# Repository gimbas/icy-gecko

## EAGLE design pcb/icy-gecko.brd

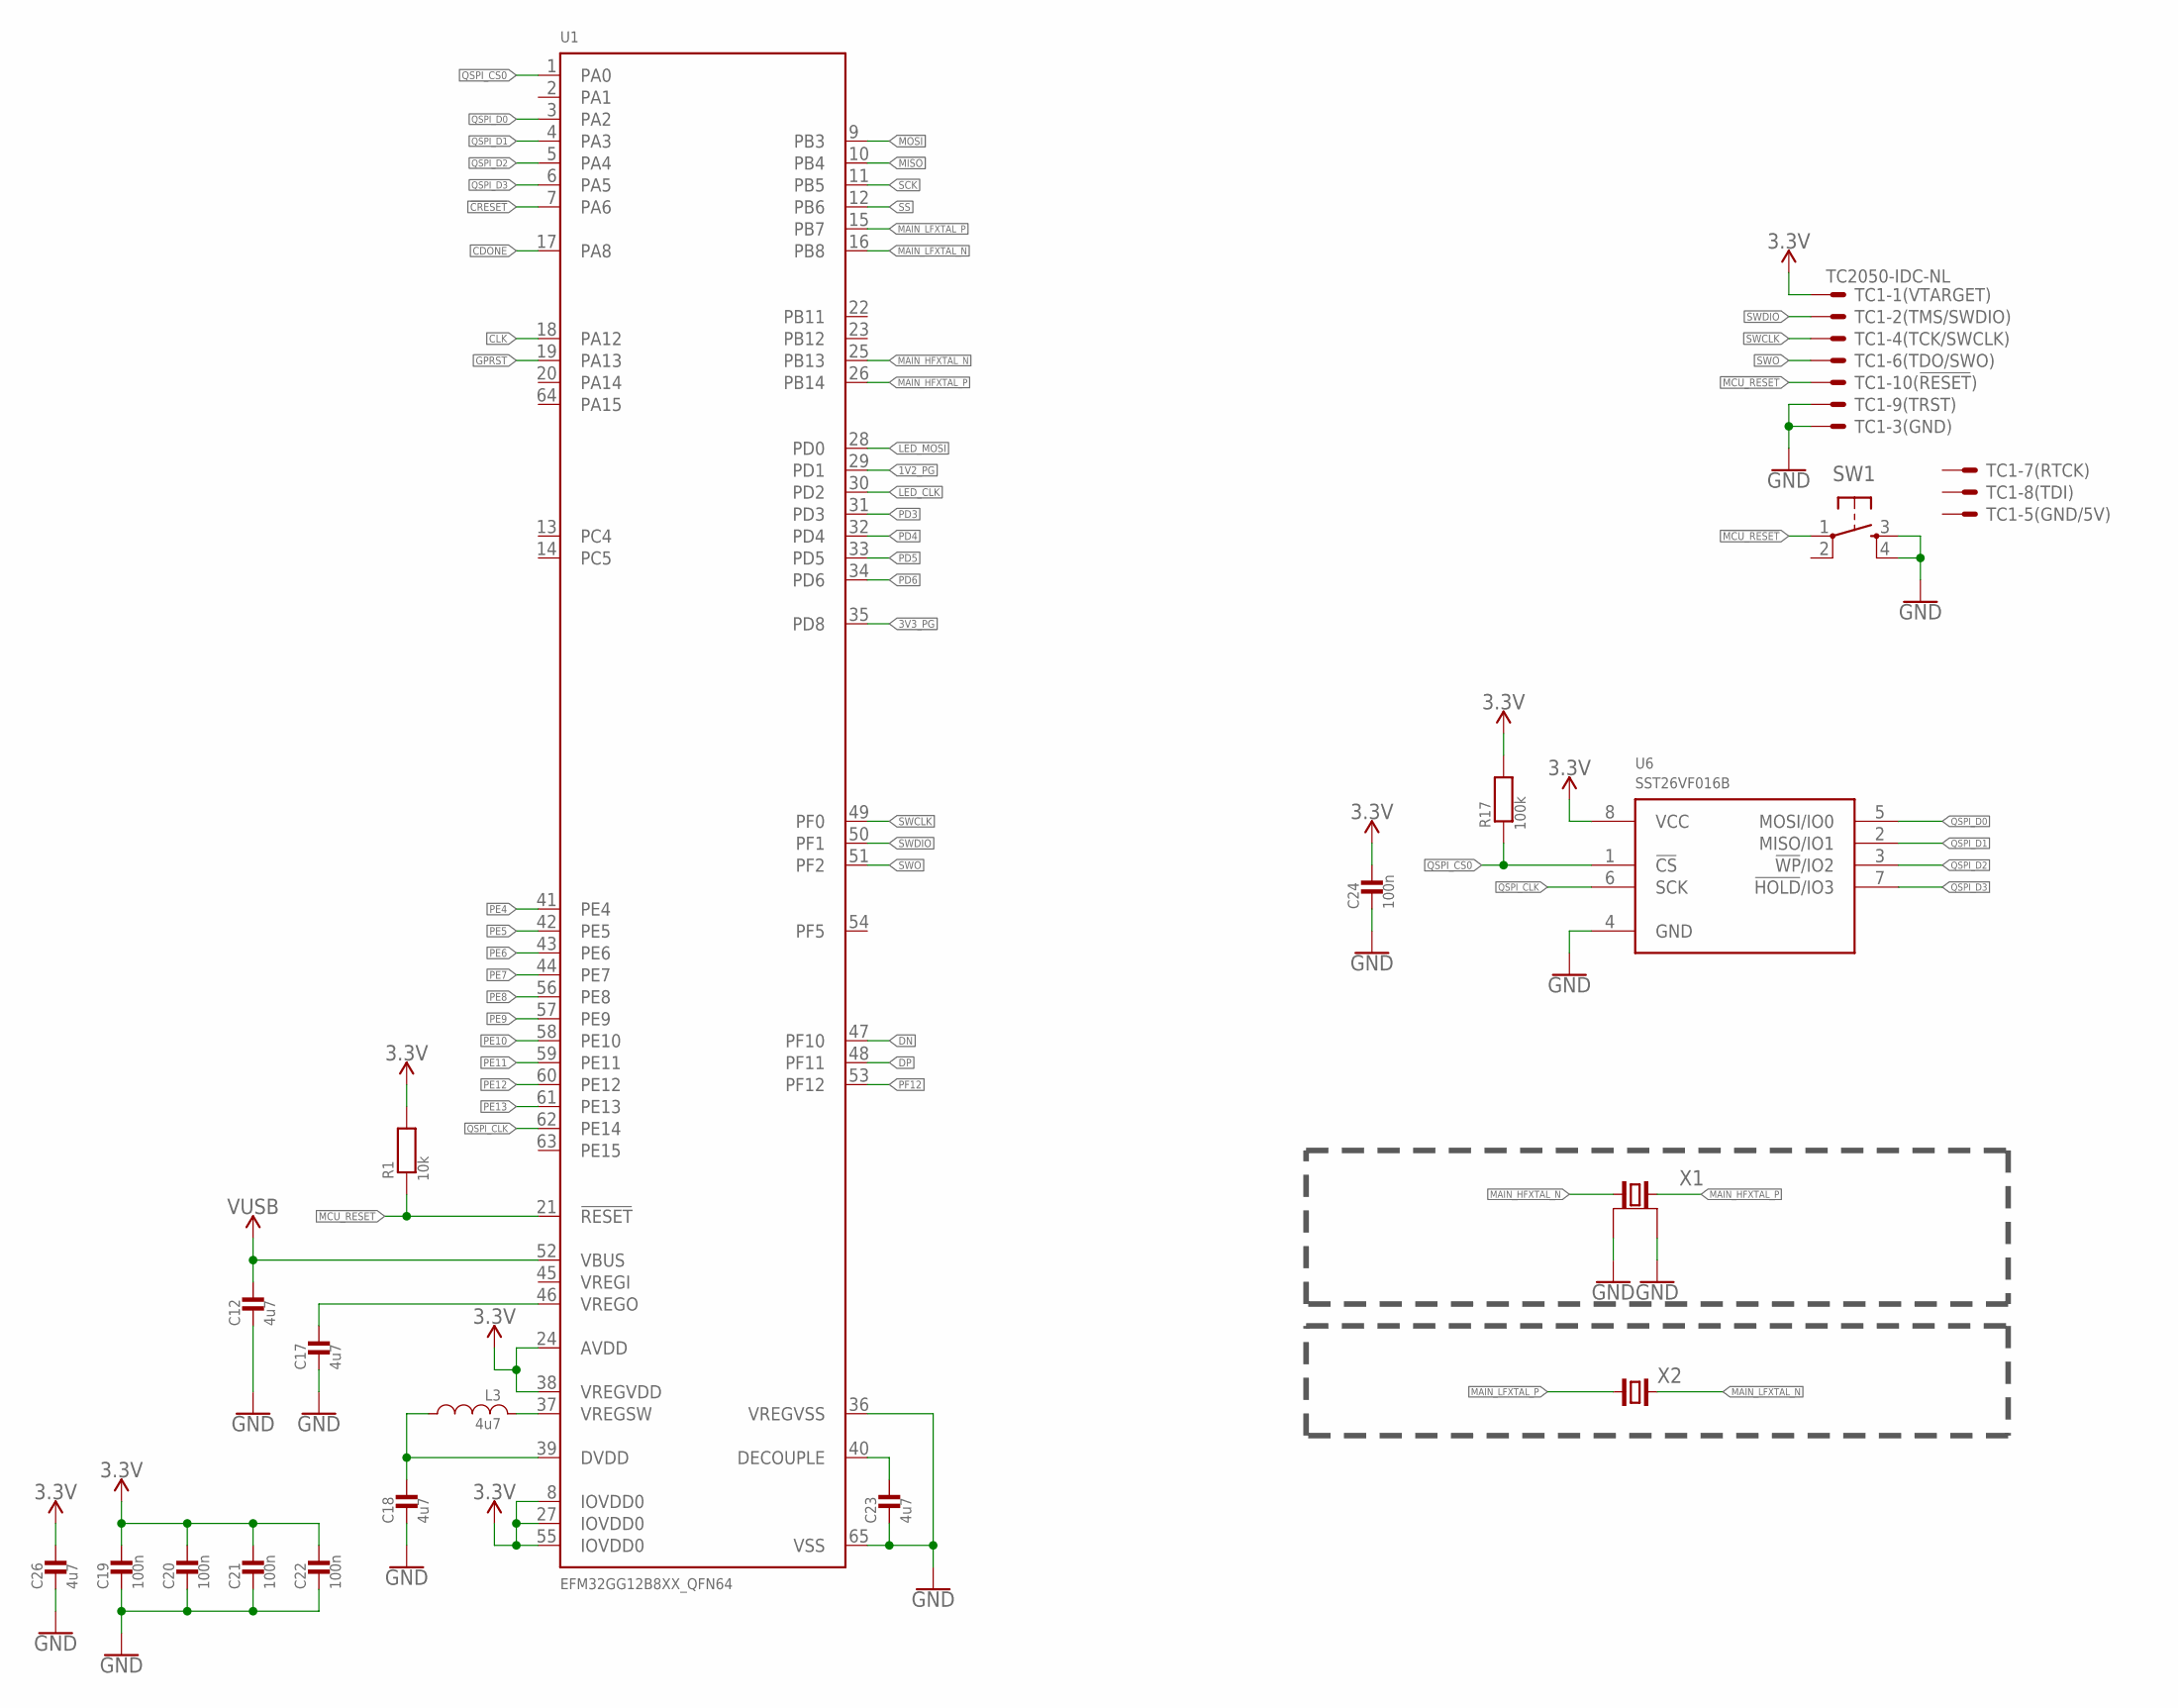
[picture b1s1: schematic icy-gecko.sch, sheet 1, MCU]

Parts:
C12, C17, C18, C23, C26: 4u7; 0603_WAVE
C19, C20, C21, C22, C24: 100n; 0603_WAVE
L3: 4u7; _0806
R1: 10k; 0603_WAVE
R17: 100k; 0603_WAVE
SW1: PUSH_BUTTON
TC1: TC2050-IDC-NL
U1: EFM32GG12B8XX_QFN64; QFN64
U6: SST26VF016B; WSOIC8
X1: CRYSTAL_4P; 4-SMD-3225
X2: CRYSTAL2-SMD-3215; 2-SMD-3215

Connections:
1V2_PG: U1.29 (PD1); also elsewhere on the board
3.3V: C19.P$1, C20.P$1, C21.P$1, C22.P$1, C24.P$1, C26.P$1, R1.P$2, R17.P$2, TC1.1, U1.8 (IOVDD0), U1.24 (AVDD), U1.27 (IOVDD0), U1.38 (VREGVDD), U1.55 (IOVDD0), U6.8 (VCC); also elsewhere on the board
3V3_PG: U1.35 (PD8); also elsewhere on the board
!CRESET: U1.7 (PA6); also elsewhere on the board
!MCU_RESET: R1.P$1, SW1.1, TC1.10, U1.21 (!RESET)
CDONE: U1.17 (PA8); also elsewhere on the board
CLK: U1.18 (PA12); also elsewhere on the board
DN: U1.47 (PF10); also elsewhere on the board
DP: U1.48 (PF11); also elsewhere on the board
GND: C12.P$2, C17.P$2, C18.P$2, C19.P$2, C20.P$2, C21.P$2, C22.P$2, C23.P$2, C24.P$2, C26.P$2, SW1.3, SW1.4, TC1.3, TC1.9, U1.36 (VREGVSS), U1.65 (VSS), U6.4 (GND), X1.2 (GND), X1.4 (GND); also elsewhere on the board
GPRST: U1.19 (PA13); also elsewhere on the board
LED_CLK: U1.30 (PD2); also elsewhere on the board
LED_MOSI: U1.28 (PD0); also elsewhere on the board
MAIN_HFXTAL_N: U1.25 (PB13), X1.1
MAIN_HFXTAL_P: U1.26 (PB14), X1.3 (2)
MAIN_LFXTAL_N: U1.16 (PB8), X2.2
MAIN_LFXTAL_P: U1.15 (PB7), X2.1
MISO: U1.10 (PB4); also elsewhere on the board
MOSI: U1.9 (PB3); also elsewhere on the board
unnamed: C17.P$1, U1.46 (VREGO)
unnamed: L3.1, U1.37 (VREGSW)
unnamed: C23.P$1, U1.40 (DECOUPLE)
unnamed: C18.P$1, L3.2, U1.39 (DVDD)
PD3: U1.31 (PD3); also elsewhere on the board
PD4: U1.32 (PD4); also elsewhere on the board
PD5: U1.33 (PD5); also elsewhere on the board
PD6: U1.34 (PD6); also elsewhere on the board
PE4: U1.41 (PE4); also elsewhere on the board
PE5: U1.42 (PE5); also elsewhere on the board
PE6: U1.43 (PE6); also elsewhere on the board
PE7: U1.44 (PE7); also elsewhere on the board
PE8: U1.56 (PE8); also elsewhere on the board
PE9: U1.57 (PE9); also elsewhere on the board
PE10: U1.58 (PE10); also elsewhere on the board
PE11: U1.59 (PE11); also elsewhere on the board
PE12: U1.60 (PE12); also elsewhere on the board
PE13: U1.61 (PE13); also elsewhere on the board
PF12: U1.53 (PF12); also elsewhere on the board
QSPI_CLK: U1.62 (PE14), U6.6 (SCK)
QSPI_CS0: R17.P$1, U1.1 (PA0), U6.1 (!CS!)
QSPI_D0: U1.3 (PA2), U6.5 (MOSI/IO0)
QSPI_D1: U1.4 (PA3), U6.2 (MISO/IO1)
QSPI_D2: U1.5 (PA4), U6.3 (!WP!/IO2)
QSPI_D3: U1.6 (PA5), U6.7 (!HOLD!/IO3)
SCK: U1.11 (PB5); also elsewhere on the board
SS: U1.12 (PB6); also elsewhere on the board
SWCLK: TC1.4, U1.49 (PF0)
SWDIO: TC1.2, U1.50 (PF1)
SWO: TC1.6, U1.51 (PF2)
VUSB: C12.P$1, U1.52 (VBUS); also elsewhere on the board

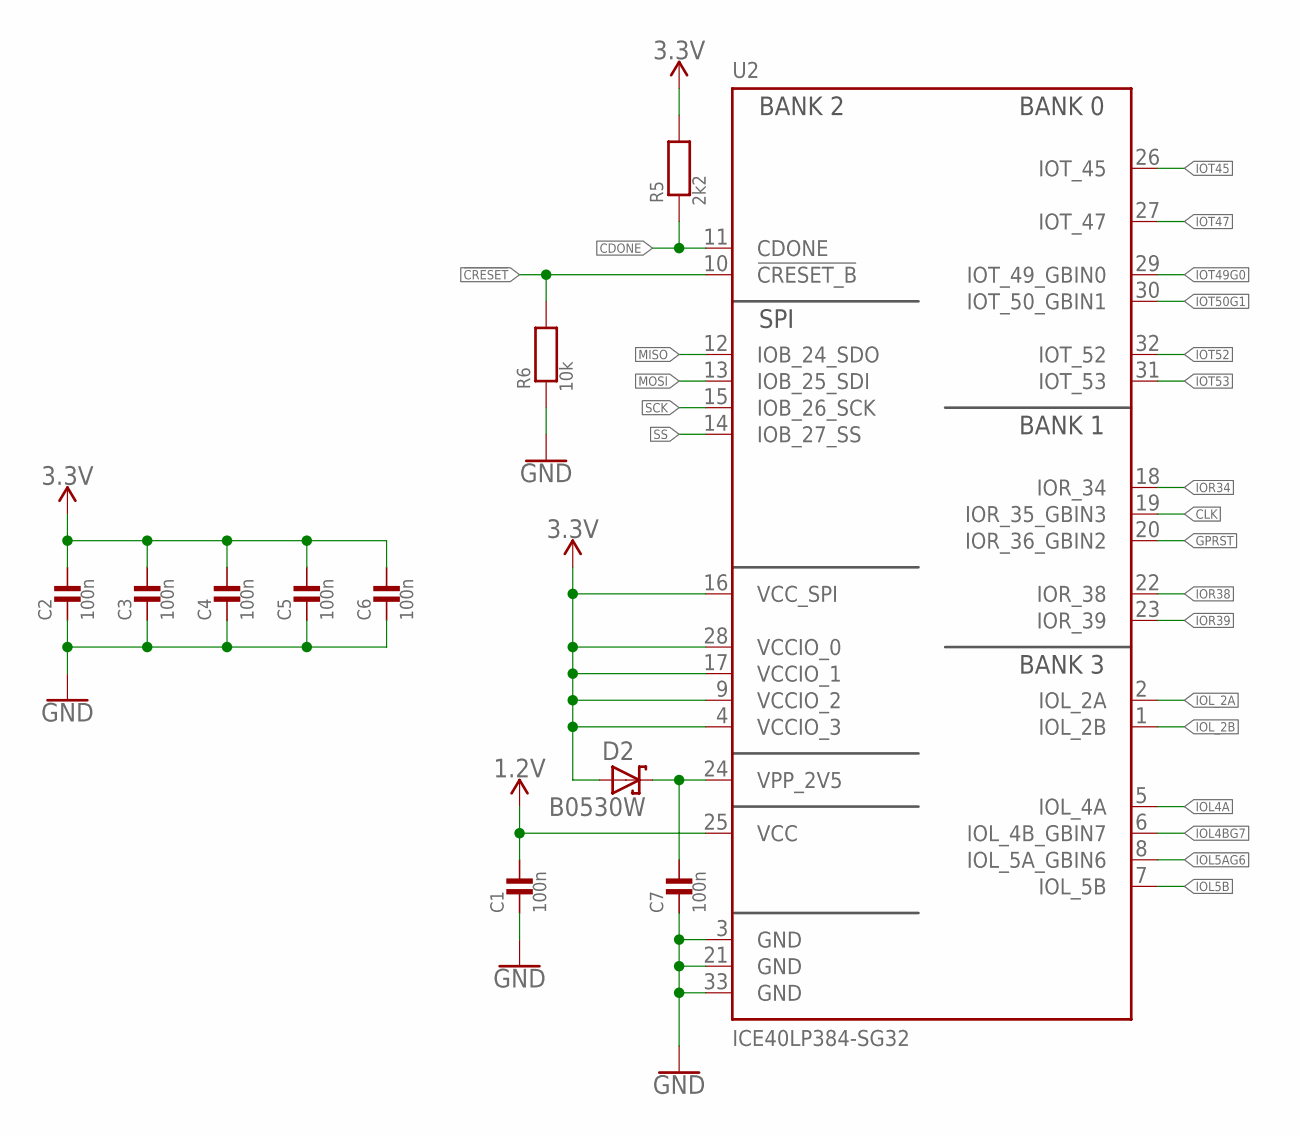
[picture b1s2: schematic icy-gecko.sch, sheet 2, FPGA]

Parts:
C1, C2, C3, C4, C5, C6, C7: 100n; 0603_WAVE
D2: B0530W; SOD-123
R5: 2k2; 0603_WAVE
R6: 10k; 0603_WAVE
U2: ICE40LP384-SG32; QFN32

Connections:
1.2V: C1.P$1, U2.25 (VCC); also elsewhere on the board
3.3V: C2.P$1, C3.P$1, C4.P$1, C5.P$1, C6.P$1, D2.A, R5.P$2, U2.4 (VCCIO_3), U2.9 (VCCIO_2), U2.16 (VCC_SPI), U2.17 (VCCIO_1), U2.28 (VCCIO_0); also elsewhere on the board
!CRESET: R6.P$2, U2.10 (!CRESET_B); also elsewhere on the board
CDONE: R5.P$1, U2.11 (CDONE); also elsewhere on the board
CLK: U2.19 (IOR_35_GBIN3); also elsewhere on the board
GND: C1.P$2, C2.P$2, C3.P$2, C4.P$2, C5.P$2, C6.P$2, C7.P$2, R6.P$1, U2.3 (GND), U2.21 (GND), U2.33 (GND); also elsewhere on the board
GPRST: U2.20 (IOR_36_GBIN2); also elsewhere on the board
IOL4A: U2.5 (IOL_4A); also elsewhere on the board
IOL4BG7: U2.6 (IOL_4B_GBIN7); also elsewhere on the board
IOL5AG6: U2.8 (IOL_5A_GBIN6); also elsewhere on the board
IOL5B: U2.7 (IOL_5B); also elsewhere on the board
IOL_2A: U2.2 (IOL_2A); also elsewhere on the board
IOL_2B: U2.1 (IOL_2B); also elsewhere on the board
IOR34: U2.18 (IOR_34); also elsewhere on the board
IOR38: U2.22 (IOR_38); also elsewhere on the board
IOR39: U2.23 (IOR_39); also elsewhere on the board
IOT45: U2.26 (IOT_45); also elsewhere on the board
IOT47: U2.27 (IOT_47); also elsewhere on the board
IOT49G0: U2.29 (IOT_49_GBIN0); also elsewhere on the board
IOT50G1: U2.30 (IOT_50_GBIN1); also elsewhere on the board
IOT52: U2.32 (IOT_52); also elsewhere on the board
IOT53: U2.31 (IOT_53); also elsewhere on the board
MISO: U2.12 (IOB_24_SDO); also elsewhere on the board
MOSI: U2.13 (IOB_25_SDI); also elsewhere on the board
unnamed: C7.P$1, D2.C, U2.24 (VPP_2V5)
SCK: U2.15 (IOB_26_SCK); also elsewhere on the board
SS: U2.14 (IOB_27_SS); also elsewhere on the board

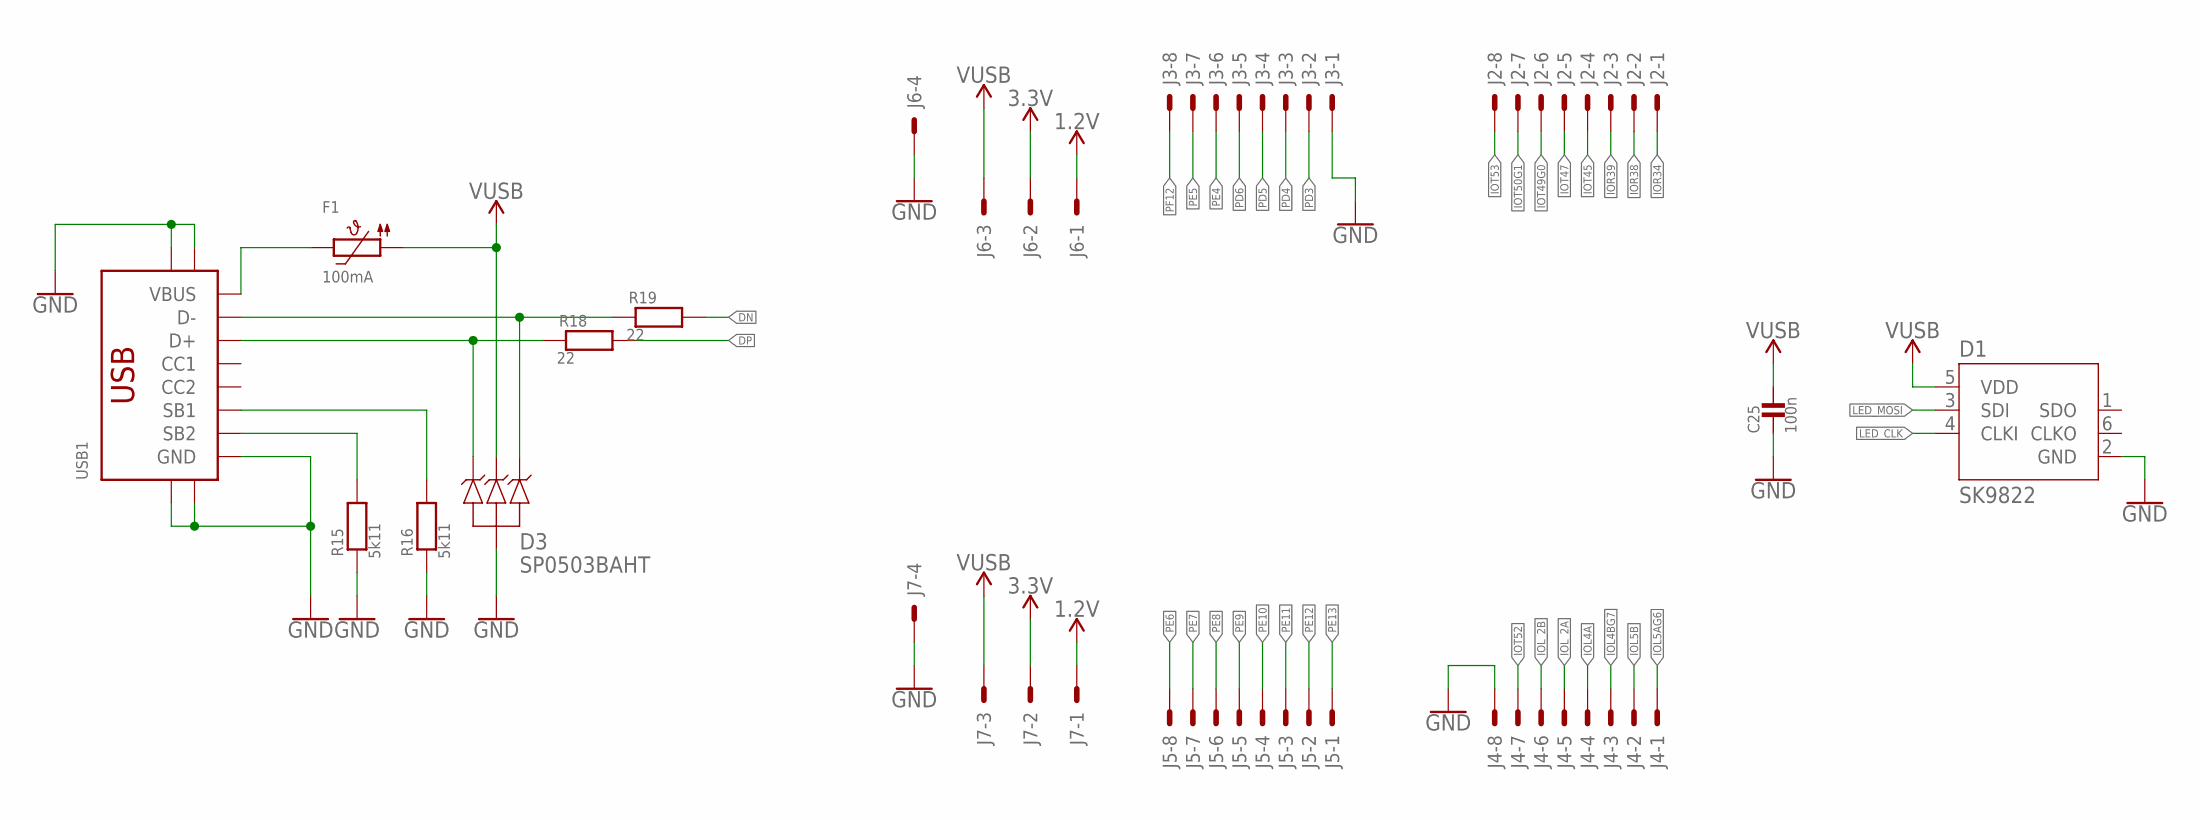
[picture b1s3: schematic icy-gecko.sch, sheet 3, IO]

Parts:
C25: 100n; 0603_WAVE
D1: SK9822; 2020
D3: SP0503BAHT; SOT143
F1: 100mA; 0805
J2, J3, J4, J5: 8; 1X8_2.54
J6, J7: 4; 1X4_2.54
R15, R16: 5k11; 0603_WAVE
R18, R19: 22; 0603_WAVE
USB1: USB-C-16P-SMD-FLAT-SIDE-TYPE-2

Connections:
1.2V: J6.1, J7.1; also elsewhere on the board
3.3V: J6.2, J7.2; also elsewhere on the board
DN: R19.P$2; also elsewhere on the board
DP: R18.P$2; also elsewhere on the board
GND: C25.P$2, D1.2 (GND), D3.1, J3.1, J4.8, J6.4, J7.4, R15.P$1, R16.P$1, USB1.A1/B12 (GND), USB1.B1/A12 (GND), USB1.SHIELD@0 (SHIELD), USB1.SHIELD@1 (SHIELD), USB1.SHIELD@2 (SHIELD), USB1.SHIELD@3 (SHIELD); also elsewhere on the board
IOL4A: J4.4; also elsewhere on the board
IOL4BG7: J4.3; also elsewhere on the board
IOL5AG6: J4.1; also elsewhere on the board
IOL5B: J4.2; also elsewhere on the board
IOL_2A: J4.5; also elsewhere on the board
IOL_2B: J4.6; also elsewhere on the board
IOR34: J2.1; also elsewhere on the board
IOR38: J2.2; also elsewhere on the board
IOR39: J2.3; also elsewhere on the board
IOT45: J2.4; also elsewhere on the board
IOT47: J2.5; also elsewhere on the board
IOT49G0: J2.6; also elsewhere on the board
IOT50G1: J2.7; also elsewhere on the board
IOT52: J4.7; also elsewhere on the board
IOT53: J2.8; also elsewhere on the board
LED_CLK: D1.4 (CLKI); also elsewhere on the board
LED_MOSI: D1.3 (SDI); also elsewhere on the board
unnamed: F1.2, USB1.A4/B9 (VBUS), USB1.B4/A9 (VBUS)
unnamed: R15.P$2, USB1.B8 (SB2)
unnamed: R16.P$2, USB1.A8 (SB1)
PD3: J3.2; also elsewhere on the board
PD4: J3.3; also elsewhere on the board
PD5: J3.4; also elsewhere on the board
PD6: J3.5; also elsewhere on the board
PE4: J3.6; also elsewhere on the board
PE5: J3.7; also elsewhere on the board
PE6: J5.8; also elsewhere on the board
PE7: J5.7; also elsewhere on the board
PE8: J5.6; also elsewhere on the board
PE9: J5.5; also elsewhere on the board
PE10: J5.4; also elsewhere on the board
PE11: J5.3; also elsewhere on the board
PE12: J5.2; also elsewhere on the board
PE13: J5.1; also elsewhere on the board
PF12: J3.8; also elsewhere on the board
USBDN: D3.4, R19.P$1, USB1.A7 (D-), USB1.B7 (D-)
USBDP: D3.2, R18.P$1, USB1.A6 (D+), USB1.B6 (D+)
VUSB: C25.P$1, D1.5 (VDD), D3.3, F1.1, J6.3, J7.3; also elsewhere on the board

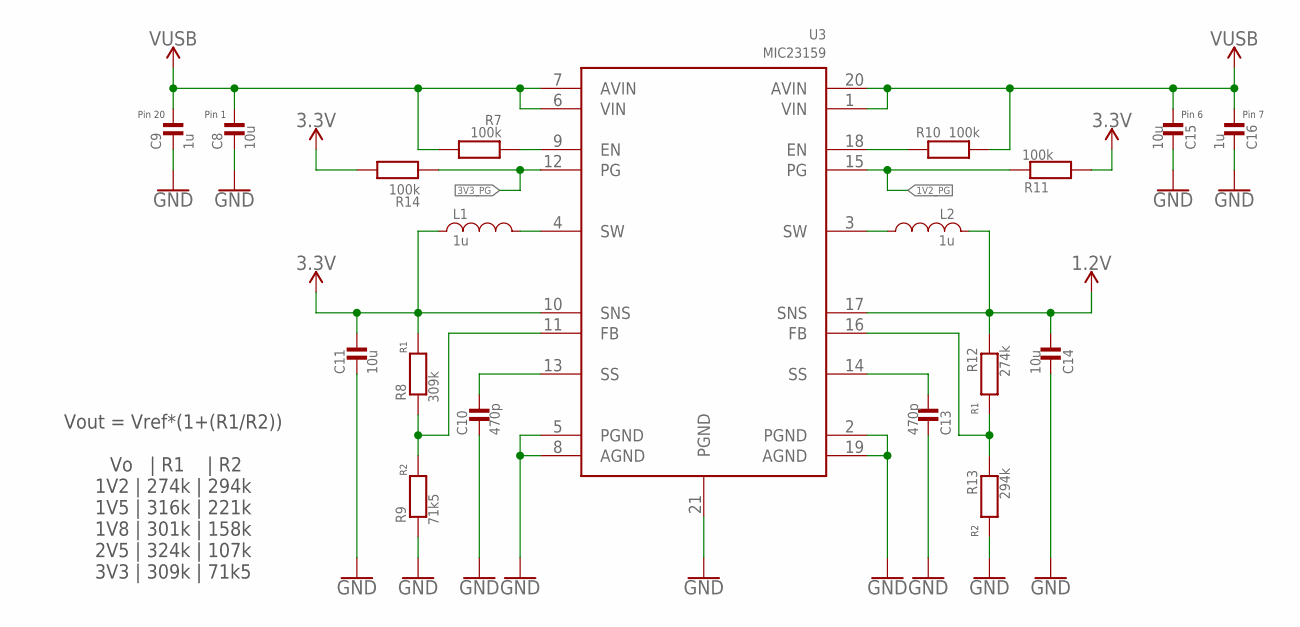
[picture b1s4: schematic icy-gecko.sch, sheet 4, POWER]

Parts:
C8, C11, C14, C15: 10u; 0603_WAVE
C9, C16: 1u; 0603_WAVE
C10, C13: 470p; 0603_WAVE
L1, L2: 1u; _0806
R7, R10, R11, R14: 100k; 0603_WAVE
R8: 309k; 0603_WAVE
R9: 71k5; 0603_WAVE
R12: 274k; 0603_WAVE
R13: 294k; 0603_WAVE
U3: MIC23159; VQFN20

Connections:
1.2V: C14.P$1, L2.1, R12.P$1, U3.17 (SNS); also elsewhere on the board
1V2_PG: R11.P$1, U3.15 (PG); also elsewhere on the board
3.3V: C11.P$1, L1.1, R8.P$2, R11.P$2, R14.P$2, U3.10 (SNS); also elsewhere on the board
3V3_PG: R14.P$1, U3.12 (PG); also elsewhere on the board
GND: C8.P$2, C9.P$2, C10.P$2, C11.P$2, C13.P$2, C14.P$2, C15.P$2, C16.P$2, R9.P$1, R13.P$2, U3.2 (PGND), U3.5 (PGND), U3.8 (AGND), U3.19 (AGND), U3.21 (PGND); also elsewhere on the board
MPU_PWR: R10.P$1, U3.18 (EN)
unnamed: R7.P$1, U3.9 (EN)
unnamed: L1.2, U3.4 (SW)
unnamed: C10.P$1, U3.13 (SS)
unnamed: R8.P$1, R9.P$2, U3.11 (FB)
unnamed: L2.2, U3.3 (SW)
unnamed: C13.P$1, U3.14 (SS)
unnamed: R12.P$2, R13.P$1, U3.16 (FB)
VUSB: C8.P$1, C9.P$1, C15.P$1, C16.P$1, R7.P$2, R10.P$2, U3.1 (VIN), U3.6 (VIN), U3.7 (AVIN), U3.20 (AVIN); also elsewhere on the board

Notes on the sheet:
Pin 20
Pin 1
Pin 7
Pin 6
Vout = Vref*(1+(R1/R2)) Vo | R1 | R2 1V2 | 274k | 294k 1V5 | 316k | 221k 1V8 | 301k | 158k 2V5 | 324k | 107k 3V3 | 309k | 71k5

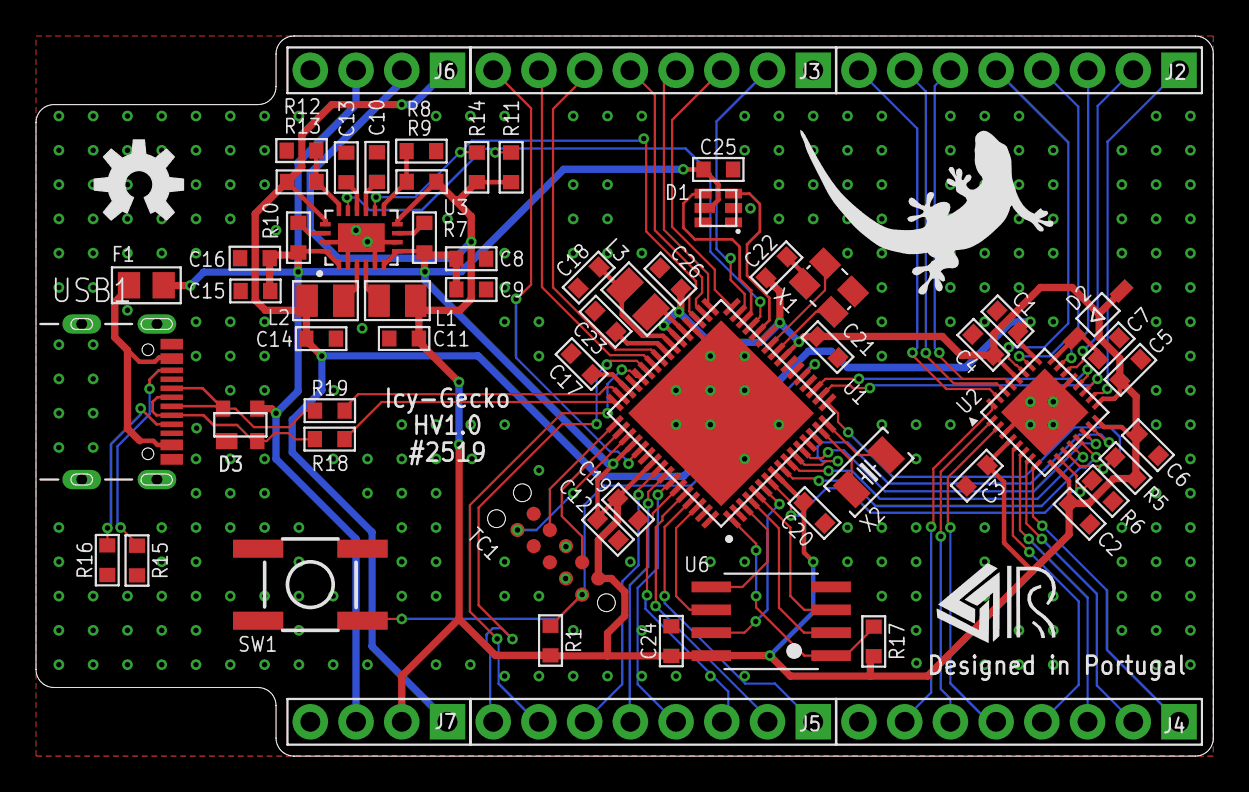
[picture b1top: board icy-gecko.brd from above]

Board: 2 copper layers, 65.4 x 40.0 mm, 67 parts (0 on the bottom side), 80 nets.

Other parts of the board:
U$1: GECKO_POLY
U$2: OSHW-LOGO-M
U$3: RAFAEL_SILVA_5MM_ALT_3

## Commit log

2019-06-17 root commit
2019-06-17 sch work
2019-06-21 finish sch, scrap pcb
2019-06-21 pcd finito
2019-09-19 sync
2020-01-18 corrected some pcb errors

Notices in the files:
pcb/icy-gecko.sch:
LICENSE: GNU General Public License v3.0
